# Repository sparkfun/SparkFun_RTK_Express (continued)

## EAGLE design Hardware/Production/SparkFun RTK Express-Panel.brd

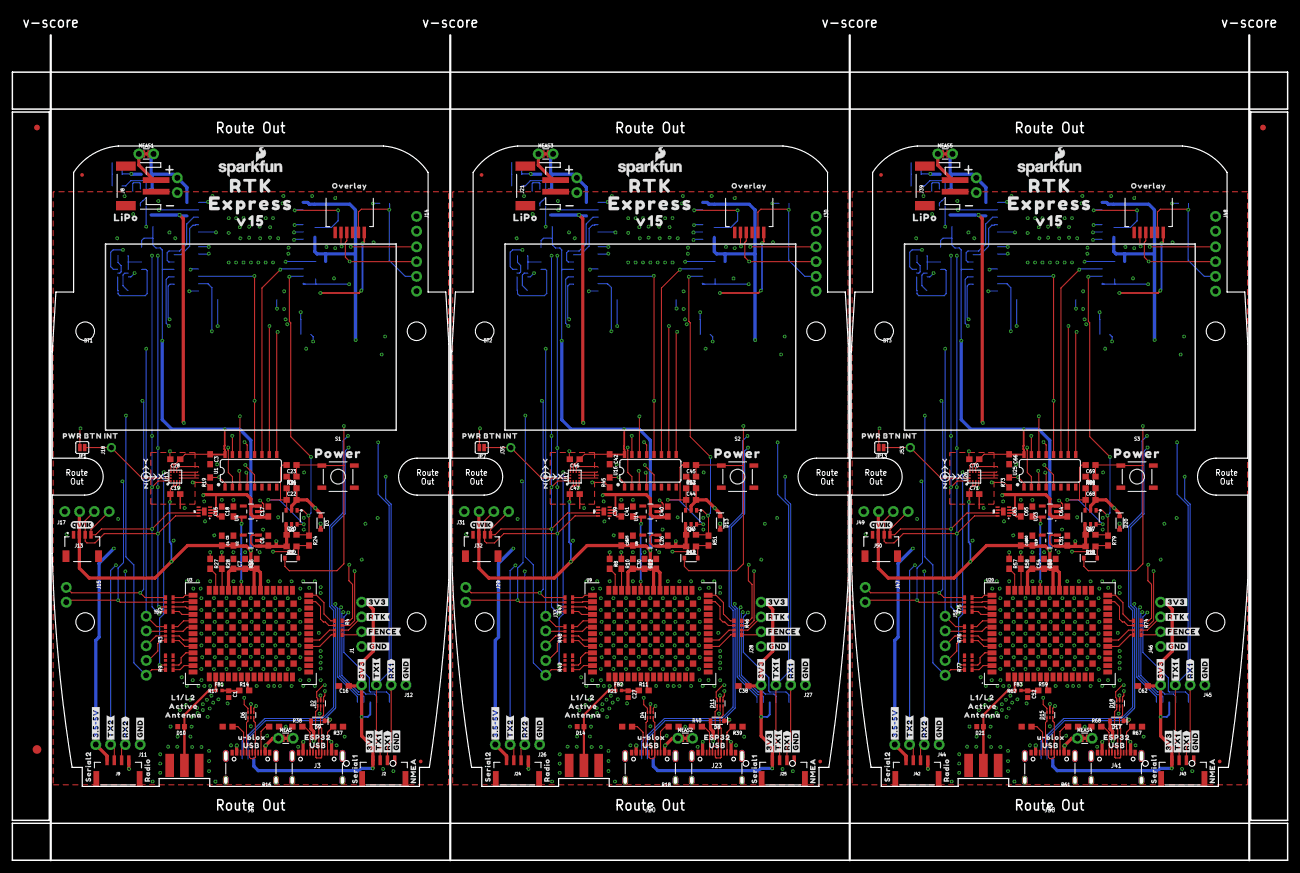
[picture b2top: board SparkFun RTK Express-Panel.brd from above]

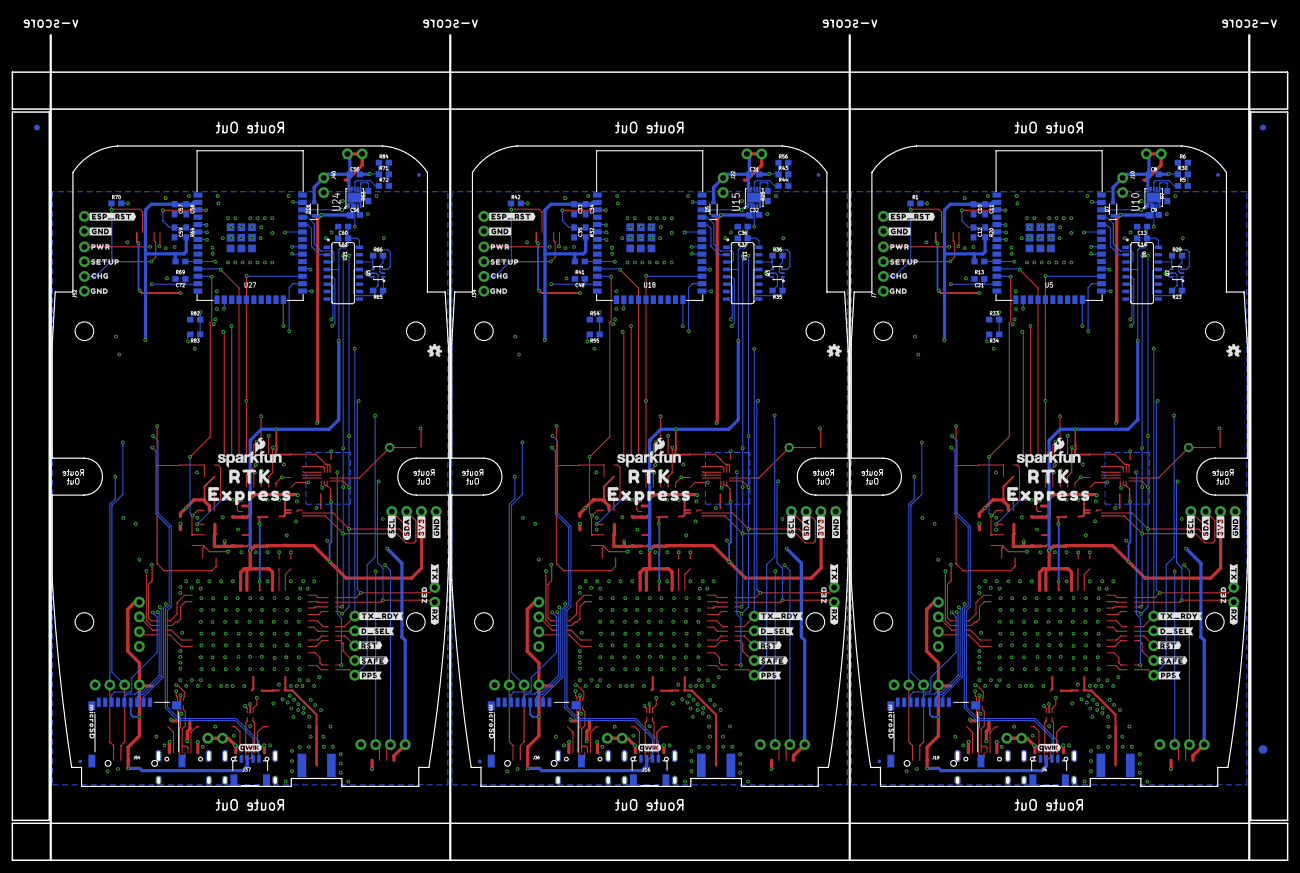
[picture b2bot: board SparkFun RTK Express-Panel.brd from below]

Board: 4 copper layers, 219.3 x 141.9 mm, 501 parts (165 on the bottom side), 258 nets.

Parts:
BT1, BT2, BT3: LIPO-OUTLINE1000; LIPO-1000
C1, C27, C52: 47pF; 0402
C2, C4, C6, C17, C18, C24, C26, C29, C40, C41, C49, C51, C53, C64, C65: 1.0uF; 0603
C3, C5, C7, C11, C12, C13, C15, C16, C21, C22, C23, C25, C28, C30, C34, C35, C36, C38, C39, C42, C44, C45, C46, C48, C50, C54, C58, C59, C60, C62, C63, C66, C68, C69, C70, C72: 0.1uF; 0603
C8, C9, C31, C32, C55, C56: 4.7uF; 0603
C10, C14, C19, C20, C33, C37, C43, C47, C57, C61, C67, C71: 10uF; 0603
D1, D12, D19: 250mA/100V; SOD-323
D2, D4, D6, D11, D15, D18: PRTR5V0U2F; SOT886
D3, D5, D7, D8, D9, D13, D16, D17, D20: 3A/10V/280mV; SOD-323
D10, D14, D21: PESD0402-0402; 0402
E1, E2, E3: SMA; SMA-EDGE
E$1, E$2, E$3, E$4: FIDUCIAL-1X2
E$5, E$6: FIDUCIAL-1.5X3
FB1, FB2, FB3: 2.66Ω; 0402-TIGHT
J1, J7, J11, J12, J26, J27, J28, J34, J44, J45, J46, J52: 1X04_NO_SILK
J2, J9, J24, J25, J42, J43: JST-4-SMD-1.25MM-LOCKING
J3, J5, J20, J23, J38, J41: USB Female Type C Connector; USB-C-16P_4LAYER-PADS
J4, J16, J37: External; JST04_1MM_RA
J6, J33, J51: 1X05_NO_SILK
J8, J21, J39: JST-2-SMD
J10, J14, J15, J22, J29, J30, J40, J47, J48: 1X02_NO_SILK
J13, J32, J50: Internal; JST04_1MM_RA
J17, J31, J49: Qwiic Right Angle; 1X04_NO_SILK
J18, J35, J53: 1X01_NO_SILK
J19, J36, J54: MICROSD; MICROSD-EXTERNALPIN
JP1, JP7, JP13: JUMPER-SMT_2_NO_SILK; SMT-JUMPER_2_NO_SILK
JP2, JP8, JP14: FPC_6_1MM-LIF
JP3, JP4, JP5, JP6, JP9, JP10, JP11, JP12, JP21, JP61, JP71, JP81: FIDUCIALUFIDUCIAL; FIDUCIAL-MICRO
LOGO1, LOGO4, LOGO7: OSHW-LOGOMINI; OSHW-LOGO-MINI
LOGO2, LOGO3, LOGO5, LOGO6, LOGO8, LOGO9: SFE_LOGO_NAME_FLAME.1_INCH; SFE_LOGO_NAME_FLAME_.1
MEAS, MEAS1, MEAS2, MEAS3, MEAS4, MEAS5: COMBO-JUMPER_2_NC_TRACE
Q1, Q4, Q6: SIL2308-TP; SOT26
Q2, Q3, Q5: MBT3904DW1T1; SC70-6
R1, R42, R70: 470; 0603
R2, R3, R4, R9, R46, R47, R48, R49, R74, R75, R76, R77: 33; 1206_RA
R5, R44, R72: 0; 0603
R6, R23, R29, R31, R34, R35, R36, R53, R55, R56, R65, R66, R81, R83, R84: 10k; 0603
R7, R19, R25, R45, R63, R73: 1k; 0603
R8, R10, R27, R28, R57, R58: 27; 0603
R11, R14, R59: 10; 0603
R12, R13, R15, R20, R22, R26, R32, R41, R50, R52, R60, R64, R69, R78, R80: 100k; 0603
R16, R17, R18, R21, R37, R38, R39, R40, R61, R62, R67, R68: 5.1k; 0603
R24, R51, R79: 300k; 0603
R30, R43, R71: 150k; 0603
R33, R54, R82: 3.3k; 0603
S1, S2, S3: Power; TACTILE_SWITCH_SMD_5.2MM
U1, U16, U25: 74HC4052D; SO16
U2, U8, U19: AP2112K-3.3; SOT23-5
U3, U9, U20: U-BLOX_ZED-F9P; ZED-F9P
U4, U14, U23: STLQ015-3.3V; SOT23-5
U5, U18, U27: ESP-WROOM-3232D; ESP-WROOM-32D
U6, U11, U21: CH340C; SO016
U7, U12, U22: MAX17048; DFN-8
U10, U15, U24: MCP73833; DFN-10
U13, U17, U26: LIS2DH12; LGA-12-LISDH12
U$1, U$19, U$38, U$48, U$63, U$64, U$82, U$95, U$127, U$140, U$141, U$157: #GND#0
U$2, U$30, U$93, U$106, U$125, U$168: QWIIC_4MM
U$3, U$107, U$169: #TX_RDY#0
U$4, U$118, U$180: INT0
U$5, U$12, U$37, U$47, U$62, U$91, U$126, U$139, U$154: #3V3#0
U$6, U$121, U$183: L1#L20
U$7, U$74, U$99, U$100, U$161, U$162: RTK0
U$8, U$120, U$182: OVERLAY0
U$9, U$119, U$181: PWR_BTN1
U$10, U$20, U$128: #RTK#1
U$11, U$78, U$148: #PPS#0
U$13, U$122, U$184: ACTIVE1
U$14, U$79, U$149: #RX#2
U$15, U$123, U$185: ANTENNA2
U$16, U$80, U$150: ZED0
U$17, U$75, U$145: ##SAFE##5
U$18, U$124, U$186: V150
U$21, U$26, U$129: 1553DBK-ENCLOSURE
U$22, U$27, U$130: LIPO0
U$23, U$77, U$147: #3#5#5V#0
U$24, U$115, U$177: X0
U$25, U$35, U$131: U#BLOX0
U$28, U$73, U$144: ##RST##4
U$29, U$54, U$134: SERIAL10
U$31, U$108, U$170: POWER0
U$32, U$76, U$146: #FENCE#3
U$33, U$109, U$171: CHG2
U$34, U$110, U$172: GND3
U$36, U$44, U$66, U$89, U$132, U$152: USB1
U$39, U$57, U$135: #RX2#2
U$40, U$58, U$136: #TX2#1
U$41, U$111, U$173: PWR0
U$42, U$112, U$174: SETUP1
U$43, U$52, U$133: SERIAL20
U$45, U$59, U$68, U$94, U$137, U$156: #RX1#2
U$46, U$61, U$65, U$92, U$138, U$155: #TX1#1
U$49, U$69, U$142: NMEA1
U$50, U$71, U$143: RADIO0
U$51, U$53, U$113, U$114, U$175, U$176: EXPRESS0
U$55, U$116, U$178: Y1
U$56, U$117, U$179: Z2
U$60, U$98, U$160: #ESP_RST#0
U$67, U$90, U$153: ESP320
U$70, U$101, U$163: #GND#2
U$72, U$81, U$151: #TX#1
U$83, U$96, U$158: MICROSD0
U$84, U$97, U$159: #GND#1
U$85, U$102, U$164: #3V3#2
U$86, U$103, U$165: #SCL#1
U$87, U$104, U$166: #SDA#0
U$88, U$105, U$167: #D_SEL#0

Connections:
3.3V: C2.1, C3.1, C4.1, C5.2, C7.2, C10.1, C11.1, C13.1, C14.1, C16.1, C19.1, C28.1, J1.4, J2.1, J4.2, J12.4, J13.2, J17.2, J19.4, R13.2, R15.2, R20.2, R34.2, U1.16, U2.5, U3.33, U3.34, U3.38, U5.2, U6.4, U6.16, U13.2, U13.3, U13.9, U13.10
3.3V1: C24.1, C25.2, C29.1, C30.2, C33.1, C34.1, C36.1, C37.1, C38.1, C42.1, C46.1, C47.1, J16.2, J25.1, J27.4, J28.4, J31.2, J32.2, J36.4, R12.2, R32.2, R41.2, R55.2, U8.5, U9.33, U9.34, U9.38, U11.4, U11.16, U16.16, U17.2, U17.3, U17.9, U17.10, U18.2
3.3V2: C49.1, C50.2, C53.1, C54.2, C57.1, C58.1, C60.1, C61.1, C62.1, C66.1, C70.1, C71.1, J37.2, J43.1, J45.4, J46.4, J49.2, J50.2, J54.4, R60.2, R64.2, R69.2, R83.2, U19.5, U20.33, U20.34, U20.38, U21.4, U21.16, U25.16, U26.2, U26.3, U26.9, U26.10, U27.2
ANT_VCC: C1.1, FB1.2, R14.1
ANT_VCC1: C27.1, FB2.2, R11.1
ANT_VCC2: C52.1, FB3.2, R59.1
CC1: J5.A5, R17.2
CC2: J5.B5, R16.2
CC3: J3.B5, R37.2
CC4: J3.A5, R38.2
CC5: J20.A5, R21.2
CC6: J20.B5, R18.2
CC7: J23.B5, R39.2
CC8: J23.A5, R40.2
CC9: J38.A5, R62.2
CC10: J38.B5, R61.2
CC11: J41.B5, R67.2
CC12: J41.A5, R68.2
CHG_LED: R1.2, U10.3
CHG_LED1: R42.2, U15.3
CHG_LED2: R70.2, U24.3
CHG_LED_RES: J7.2, JP2.2, R1.1
CHG_LED_RES1: J34.2, JP8.2, R42.1
CHG_LED_RES2: J52.2, JP14.2, R70.1
CHG_THERM1: R5.2, R6.2, R30.2
CHG_THERM2: R43.2, R44.2, R56.2
CHG_THERM3: R71.2, R72.2, R84.2
D+: D6.4, R27.1
D+1: D2.4, U6.5
D+2: D4.4, R8.1
D+3: D11.4, U11.5
D+4: D15.4, R57.1
D+5: D18.4, U21.5
D-: D6.6, R28.1
D-1: D2.6, U6.6
D-2: D4.6, R10.1
D-3: D11.6, U11.6
D-4: D15.6, R58.1
D-5: D18.6, U21.6
ESP32_!DTR: Q2.1, R23.1, U6.13
ESP32_!DTR1: Q3.1, R35.1, U11.13
ESP32_!DTR2: Q5.1, R65.1, U21.13
ESP32_!RTS: Q2.4, R29.1, U6.14
ESP32_!RTS1: Q3.4, R36.1, U11.14
ESP32_!RTS2: Q5.4, R66.1, U21.14
ESP32_EN: C12.1, J14.1, Q2.3, R20.1, U5.3
ESP32_EN1: C35.1, J30.1, Q3.3, R32.1, U18.3
ESP32_EN2: C59.1, J48.1, Q5.3, R64.1, U27.3
ESP32_RXI: U5.34, U6.2
ESP32_RXI1: U11.2, U18.34
ESP32_RXI2: U21.2, U27.34
ESP32_TXO: U5.35, U6.3
ESP32_TXO1: U11.3, U18.35
ESP32_TXO2: U21.3, U27.35
ESP_0/BOOT: Q2.6, U5.25
ESP_0/BOOT1: Q3.6, U18.25
ESP_0/BOOT2: Q5.6, U27.25
ESP_2/MUX_A: U1.10, U5.24
ESP_2/MUX_A1: U16.10, U18.24
ESP_2/MUX_A2: U25.10, U27.24
ESP_4/ACCEL_INT: J18.1, JP1.1, U13.12
ESP_4/ACCEL_INT1: J35.1, JP7.1, U17.12
ESP_4/ACCEL_INT2: J53.1, JP13.1, U26.12
ESP_4/MUX_B: U1.9, U5.26
ESP_4/MUX_B1: U16.9, U18.26
ESP_4/MUX_B2: U25.9, U27.26
ESP_13/POWER_CTRL: D1.A, R22.1, R24.2, U5.16
ESP_13/POWER_CTRL1: D12.A, R50.1, R51.2, U18.16
ESP_13/POWER_CTRL2: D19.A, R78.1, R79.2, U27.16
ESP_14/SETUP_BUTTON: C21.1, J7.3, JP2.4, U5.13
ESP_14/SETUP_BUTTON1: C48.1, J34.3, JP8.4, U18.13
ESP_14/SETUP_BUTTON2: C72.1, J52.3, JP14.4, U27.13
ESP_18/SCK: J19.5, U5.30
ESP_18/SCK1: J36.5, U18.30
ESP_18/SCK2: J54.5, U27.30
ESP_19/CIPO: J19.7, U5.31
ESP_19/CIPO1: J36.7, U18.31
ESP_19/CIPO2: J54.7, U27.31
ESP_21/SDA: J4.3, J13.3, J17.3, R2.P7, U1.2, U5.33, U7.8, U13.4
ESP_21/SDA1: J16.3, J31.3, J32.3, R47.P7, U12.8, U16.2, U17.4, U18.33
ESP_21/SDA2: J37.3, J49.3, J50.3, R75.P7, U22.8, U25.2, U26.4, U27.33
ESP_22/SCL: J4.4, J13.4, J17.4, R2.P8, U1.15, U5.36, U7.7, U13.1
ESP_22/SCL1: J16.4, J31.4, J32.4, R47.P8, U12.7, U16.15, U17.1, U18.36
ESP_22/SCL2: J37.4, J49.4, J50.4, R75.P8, U22.7, U25.15, U26.1, U27.36
ESP_23/COPI: J19.3, U5.37
ESP_23/COPI1: J36.3, U18.37
ESP_23/COPI2: J54.3, U27.37
ESP_25/SD_!CS!: J19.2, R13.1, U5.10
ESP_25/SD_!CS!1: J36.2, R41.1, U18.10
ESP_25/SD_!CS!2: J54.2, R69.1, U27.10
ESP_26/DAC1: U16.11, U18.11
ESP_26/DAC2: U1.11, U5.11
ESP_26/DAC3: U25.11, U27.11
ESP_26/ZED_TX_READY_LV: R3.P4, U3.46
ESP_26/ZED_TX_READY_LV1: R48.P4, U9.46
ESP_26/ZED_TX_READY_LV2: R76.P4, U20.46
ESP_27/FAST_OFF: C20.2, Q1.G1, R24.1, U5.12
ESP_27/FAST_OFF1: C43.2, Q4.G1, R51.1, U18.12
ESP_27/FAST_OFF2: C67.2, Q6.G1, R79.1, U27.12
ESP_D1+: D2.3, J3.A6, J3.B6
ESP_D1+1: D11.3, J23.A6, J23.B6
ESP_D1+2: D18.3, J41.A6, J41.B6
ESP_D1-: D2.1, J3.A7, J3.B7
ESP_D1-1: D11.1, J23.A7, J23.B7
ESP_D1-2: D18.1, J41.A7, J41.B7
ESP_I16/ZED-TXO1: J15.1, R2.P5, U1.12, U5.27
ESP_I16/ZED-TXO2: J29.1, R47.P5, U16.12, U18.27
ESP_I16/ZED-TXO3: J47.1, R75.P5, U25.12, U27.27
ESP_I34/ZED_TX_READY: J6.1, R3.P5, U5.6
ESP_I34/ZED_TX_READY1: J33.1, R48.P5, U18.6
ESP_I34/ZED_TX_READY2: J51.1, R76.P5, U27.6
ESP_I35/DEVICE_SENSE: R33.2, R34.1, U5.7
ESP_I35/DEVICE_SENSE1: R54.2, R55.1, U18.7
ESP_I35/DEVICE_SENSE2: R82.2, R83.1, U27.7
ESP_I39/ADC1: U16.4, U18.5
ESP_I39/ADC2: U25.4, U27.5
ESP_I39/ADC39: U1.4, U5.5
ESP_O17/ZED-RXI1: J15.2, R2.P6, R19.2, U1.1
ESP_O17/ZED-RXI2: J29.2, R45.2, R47.P6, U16.1
ESP_O17/ZED-RXI3: J47.2, R73.2, R75.P6, U25.1
EXTERNAL_DATA_IN: J2.3, J12.2, U1.3
EXTERNAL_DATA_IN1: J25.3, J27.2, U16.3
EXTERNAL_DATA_IN2: J43.3, J45.2, U25.3
EXTERNAL_DATA_OUT: J2.2, J12.3, U1.13
EXTERNAL_DATA_OUT1: J25.2, J27.3, U16.13
EXTERNAL_DATA_OUT2: J43.2, J45.3, U25.13
EXTINT_LV: R9.P2, U3.51
EXTINT_LV1: R49.P2, U9.51
EXTINT_LV2: R77.P2, U20.51
FENCE_LV: R4.P4, U3.19
FENCE_LV1: R46.P4, U9.19
FENCE_LV2: R74.P4, U20.19
GND: C1.2, C2.2, C3.2, C4.2, C5.1, C6.2, C7.1, C8.2, C9.2, C10.2, C11.2, C12.2, C13.2, C14.2, C15.2, C16.2, C17.2, C18.2, C19.2, C21.2, C28.2, D2.2, D6.2, D10.2, E1.GND@0, E1.GND@1, E1.GND@2, E1.GND@3, J1.1, J2.4, J3.GND, J3.GND2, J3.SHLD1, J3.SHLD2, J3.SHLD3, J3.SHLD4, J4.1, J5.GND, J5.GND2, J5.SHLD1, J5.SHLD2, J5.SHLD3, J5.SHLD4, J7.1, J8.1, J9.4, J10.2, J11.1, J12.1, J13.1, J14.2, J17.1, J19.6, J19.9, J19.10, J19.11, J19.12, J19.13, JP2.6, Q1.S1, R6.1, R7.1, R15.1, R16.1, R17.1, R30.1, R33.1, R37.1, R38.1, S1.3, U1.6, U1.7, U1.8, U2.2, U3.1, U3.3, U3.12, U3.14, U3.32, U3.37, U3.41, U3.48, U3.55, U3.56, U3.57, U3.58, U3.59, U3.60, U3.61, U3.62, U3.63, U3.64, U3.65, U3.66, U3.67, U3.68, U3.69, U3.70, U3.71, U3.72, U3.73, U3.74, U3.75, U3.76, U3.77, U3.78, U3.79, U3.80, U3.81, U3.82, U3.83, U3.84, U3.85, U3.86, U3.87, U3.88, U3.89, U3.90, U3.91, U3.92, U3.93, U3.94, U3.95, U3.96, U3.97, U3.98, U3.99, U3.100, U3.101, U3.102, U4.2, U5.1, U5.15, U5.38, U5.GND, U5.GNDT1, U5.GNDT2, U5.GNDT3, U5.GNDT4, U5.GNDT5, U5.GNDT6, U5.GNDT7, U5.GNDT8, U6.1, U7.1, U7.4, U7.6, U7.9, U10.5, U10.11, U13.5, U13.6, U13.7, U13.8
GND1: C24.2, C25.1, C26.2, C27.2, C29.2, C30.1, C31.2, C32.2, C33.2, C34.2, C35.2, C36.2, C37.2, C38.2, C39.2, C40.2, C41.2, C42.2, C46.2, C47.2, C48.2, D4.2, D11.2, D14.2, E2.GND@0, E2.GND@1, E2.GND@2, E2.GND@3, J16.1, J20.GND, J20.GND2, J20.SHLD1, J20.SHLD2, J20.SHLD3, J20.SHLD4, J21.1, J22.2, J23.GND, J23.GND2, J23.SHLD1, J23.SHLD2, J23.SHLD3, J23.SHLD4, J24.4, J25.4, J26.1, J27.1, J28.1, J30.2, J31.1, J32.1, J34.1, J36.6, J36.9, J36.10, J36.11, J36.12, J36.13, JP8.6, Q4.S1, R12.1, R18.1, R21.1, R25.1, R39.1, R40.1, R43.1, R54.1, R56.1, S2.3, U8.2, U9.1, U9.3, U9.12, U9.14, U9.32, U9.37, U9.41, U9.48, U9.55, U9.56, U9.57, U9.58, U9.59, U9.60, U9.61, U9.62, U9.63, U9.64, U9.65, U9.66, U9.67, U9.68, U9.69, U9.70, U9.71, U9.72, U9.73, U9.74, U9.75, U9.76, U9.77, U9.78, U9.79, U9.80, U9.81, U9.82, U9.83, U9.84, U9.85, U9.86, U9.87, U9.88, U9.89, U9.90, U9.91, U9.92, U9.93, U9.94, U9.95, U9.96, U9.97, U9.98, U9.99, U9.100, U9.101, U9.102, U11.1, U12.1, U12.4, U12.6, U12.9, U14.2, U15.5, U15.11, U16.6, U16.7, U16.8, U17.5, U17.6, U17.7, U17.8, U18.1, U18.15, U18.38, U18.GND, U18.GNDT1, U18.GNDT2, U18.GNDT3, U18.GNDT4, U18.GNDT5, U18.GNDT6, U18.GNDT7, U18.GNDT8
GND2: C49.2, C50.1, C51.2, C52.2, C53.2, C54.1, C55.2, C56.2, C57.2, C58.2, C59.2, C60.2, C61.2, C62.2, C63.2, C64.2, C65.2, C66.2, C70.2, C71.2, C72.2, D15.2, D18.2, D21.2, E3.GND@0, E3.GND@1, E3.GND@2, E3.GND@3, J37.1, J38.GND, J38.GND2, J38.SHLD1, J38.SHLD2, J38.SHLD3, J38.SHLD4, J39.1, J40.2, J41.GND, J41.GND2, J41.SHLD1, J41.SHLD2, J41.SHLD3, J41.SHLD4, J42.4, J43.4, J44.1, J45.1, J46.1, J48.2, J49.1, J50.1, J52.1, J54.6, J54.9, J54.10, J54.11, J54.12, J54.13, JP14.6, Q6.S1, R60.1, R61.1, R62.1, R63.1, R67.1, R68.1, R71.1, R82.1, R84.1, S3.3, U19.2, U20.1, U20.3, U20.12, U20.14, U20.32, U20.37, U20.41, U20.48, U20.55, U20.56, U20.57, U20.58, U20.59, U20.60, U20.61, U20.62, U20.63, U20.64, U20.65, U20.66, U20.67, U20.68, U20.69, U20.70, U20.71, U20.72, U20.73, U20.74, U20.75, U20.76, U20.77, U20.78, U20.79, U20.80, U20.81, U20.82, U20.83, U20.84, U20.85, U20.86, U20.87, U20.88, U20.89, U20.90, U20.91, U20.92, U20.93, U20.94, U20.95, U20.96, U20.97, U20.98, U20.99, U20.100, U20.101, U20.102, U21.1, U22.1, U22.4, U22.6, U22.9, U23.2, U24.5, U24.11, U25.6, U25.7, U25.8, U26.5, U26.6, U26.7, U26.8, U27.1, U27.15, U27.38, U27.GND, U27.GNDT1, U27.GNDT2, U27.GNDT3, U27.GNDT4, U27.GNDT5, U27.GNDT6, U27.GNDT7, U27.GNDT8
GPS_ANT1: D10.1, E1.SIG, FB1.1, U3.2
GPS_ANT2: D14.1, E2.SIG, FB2.1, U9.2
GPS_ANT3: D21.1, E3.SIG, FB3.1, U20.2
LIPO_RAW: J8.2, MEAS1.1, MEAS1.3
LIPO_RAW1: J21.2, MEAS3.1, MEAS3.3
LIPO_RAW2: J39.2, MEAS5.1, MEAS5.3
unnamed: R8.2, U9.40
unnamed: R10.2, U9.39
unnamed: R11.2, U9.7
unnamed: J5.VBUS1, J5.VBUS2, MEAS.1, MEAS.3
unnamed: R5.1, U10.8
unnamed: R19.1, U5.28
unnamed: Q3.5, R35.2
unnamed: Q3.2, R36.2
unnamed: D8.A, J23.VBUS1, J23.VBUS2
unnamed: J20.VBUS1, J20.VBUS2, MEAS2.1, MEAS2.3
unnamed: R27.2, U3.40
unnamed: R28.2, U3.39
unnamed: R14.2, U3.7
unnamed: R44.1, U15.8
unnamed: C22.1, C23.2, Q1.D1, Q1.G2, R26.1
unnamed: R45.1, U18.28
unnamed: C44.1, C45.2, Q4.D1, Q4.G2, R52.1
unnamed: R57.2, U20.40
unnamed: R58.2, U20.39
unnamed: R59.2, U20.7
unnamed: Q5.5, R65.2
unnamed: Q5.2, R66.2
unnamed: D17.A, J41.VBUS1, J41.VBUS2
unnamed: Q2.5, R23.2
unnamed: Q2.2, R29.2
unnamed: J38.VBUS1, J38.VBUS2, MEAS4.1, MEAS4.3
unnamed: R72.1, U24.8
unnamed: R73.1, U27.28
unnamed: C68.1, C69.2, Q6.D1, Q6.G2, R80.1
unnamed: D9.A, J3.VBUS1, J3.VBUS2
POWER_BTN: C23.1, D1.C, J7.4, JP1.2, JP2.5, R31.1, S1.1
POWER_BTN1: C45.1, D12.C, J34.4, JP7.2, JP8.5, R53.1, S2.1
POWER_BTN2: C69.1, D19.C, J52.4, JP13.2, JP14.5, R81.1, S3.1
PPS: R9.P1, U3.53
PPS1: R49.P1, U9.53
PPS2: R77.P1, U20.53
PROG1: R7.2, U10.6
PROG2: R25.2, U15.6
PROG3: R63.2, U24.6
RTK_LV: R4.P3, U3.20
RTK_LV1: R46.P3, U9.20
RTK_LV2: R74.P3, U20.20
RX2_LV: R4.P2, U3.26
RX2_LV1: R46.P2, U9.26
RX2_LV2: R74.P2, U20.26
RXLV: R2.P3, U3.43
RXLV1: R47.P3, U9.43
RXLV2: R75.P3, U20.43
SCL_LV: R2.P1, U3.45
SCL_LV1: R47.P1, U9.45
SCL_LV2: R75.P1, U20.45
SDA_LV: R2.P2, U3.44
SDA_LV1: R47.P2, U9.44
SDA_LV2: R75.P2, U20.44
TX2_LV: R4.P1, U3.27
TX2_LV1: R46.P1, U9.27
TX2_LV2: R74.P1, U20.27
TXLV: R2.P4, U3.42
TXLV1: R47.P4, U9.42
TXLV2: R75.P4, U20.42
UNP_D+: D6.3, J5.A6, J5.B6
UNP_D+1: D4.3, J20.A6, J20.B6
UNP_D+2: D15.3, J38.A6, J38.B6
UNP_D-: D6.1, J5.A7, J5.B7
UNP_D-1: D4.1, J20.A7, J20.B7
UNP_D-2: D15.1, J38.A7, J38.B7
VOUT: C6.1, C20.1, J9.1, J11.4, Q1.D2, R22.2, U2.1, U2.3
VOUT1: C26.1, C43.1, J24.1, J26.4, Q4.D2, R50.2, U8.1, U8.3
VOUT2: C51.1, C67.1, J42.1, J44.4, Q6.D2, R78.2, U19.1, U19.3
V_BATT: C8.1, C15.1, C17.1, D7.A, J10.1, MEAS1.2, MEAS1.4, U4.1, U4.3, U7.2, U7.3, U10.9, U10.10
V_BATT1: C31.1, C39.1, C40.1, D5.A, J22.1, MEAS3.2, MEAS3.4, U12.2, U12.3, U14.1, U14.3, U15.9, U15.10
V_BATT2: C55.1, C63.1, C64.1, D16.A, J40.1, MEAS5.2, MEAS5.4, U22.2, U22.3, U23.1, U23.3, U24.9, U24.10
V_BKCP: C18.1, U3.36, U4.5
V_BKCP1: C41.1, U9.36, U14.5
V_BKCP2: C65.1, U20.36, U23.5
V_RAW: C9.1, C22.2, D3.C, D7.C, Q1.S2, R26.2, R31.2, U10.1, U10.2
V_RAW1: C32.1, C44.2, D5.C, D13.C, Q4.S2, R52.2, R53.2, U15.1, U15.2
V_RAW2: C56.1, C68.2, D16.C, D20.C, Q6.S2, R80.2, R81.2, U24.1, U24.2
V_USB: D2.5, D3.A, D6.5, D9.C, JP2.1, MEAS.2, MEAS.4
V_USB1: D4.5, D8.C, D11.5, D13.A, JP8.1, MEAS2.2, MEAS2.4
V_USB2: D15.5, D17.C, D18.5, D20.A, JP14.1, MEAS4.2, MEAS4.4
ZED-RXI1: J24.3, J26.2, R46.P7
ZED-RXI2: J9.3, J11.2, R4.P7
ZED-RXI3: J42.3, J44.2, R74.P7
ZED-TXO1: J24.2, J26.3, R46.P8
ZED-TXO2: J9.2, J11.3, R4.P8
ZED-TXO3: J42.2, J44.3, R74.P8
ZED_!RESET!: J6.3, R3.P7
ZED_!RESET!1: J33.3, R48.P7
ZED_!RESET!2: J51.3, R76.P7
ZED_!RESET!_LV: R3.P2, U3.49
ZED_!RESET!_LV1: R48.P2, U9.49
ZED_!RESET!_LV2: R76.P2, U20.49
ZED_!SAFE!: J6.4, R3.P8
ZED_!SAFE!1: J33.4, R48.P8
ZED_!SAFE!2: J51.4, R76.P8
ZED_!SAFE!_LV: R3.P1, U3.50
ZED_!SAFE!_LV1: R48.P1, U9.50
ZED_!SAFE!_LV2: R76.P1, U20.50
ZED_D_SEL: J6.2, R3.P6
ZED_D_SEL1: J33.2, R48.P6
ZED_D_SEL2: J51.2, R76.P6
ZED_D_SEL_LV: R3.P3, U3.47
ZED_D_SEL_LV1: R48.P3, U9.47
ZED_D_SEL_LV2: R76.P3, U20.47
ZED_EXTINT: R9.P7, U1.5
ZED_EXTINT1: R49.P7, U16.5
ZED_EXTINT2: R77.P7, U25.5
ZED_FENCE_STAT: J1.2, R4.P5
ZED_FENCE_STAT1: J28.2, R46.P5
ZED_FENCE_STAT2: J46.2, R74.P5
ZED_PPS_STAT: J6.5, R9.P8, U1.14
ZED_PPS_STAT1: J33.5, R49.P8, U16.14
ZED_PPS_STAT2: J51.5, R77.P8, U25.14
ZED_RTK_STAT: J1.3, R4.P6
ZED_RTK_STAT1: J28.3, R46.P6
ZED_RTK_STAT2: J46.3, R74.P6

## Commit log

2021-02-24 Add firmware
2021-02-24 New state machine. Faster display updates. More graphics.
2021-02-24 Change Surveyor to Express in firmware
2021-02-24 Add display during serial config. Add min HPA before survey-in start.
2021-02-24 Control base/rover state based on power button tap
2021-03-04 Ready v11. Redo GND layers for panelizer.
2021-03-04 Add tilt test sketches
2021-03-04 Add helper displays for base/rover switching.
2021-03-04 Remove old libraries
2021-03-05 Add menu and NVM support for mux control.
2021-03-19 Update FP and PROD ID on ESP32 module
2021-03-26 Update graphics
2021-04-13 Modify toolpath for 1/16" Bit
2021-04-16 Move radio to power control. Add ESD to GNSS RF. Move overlay connector.
2021-04-16 Remove old sketch
2021-04-16 Add BT pin support. Add accel support. Increase xTask sizes. Increase I2C to 400kHz.
2021-04-16 Add online check for fuel gauge.
2021-04-16 Move test menu to display.
2021-04-16 Add test sketches for display, and accel.
2021-04-16 Add test sketches for Sound Trigger logging.
2021-04-16 Remove old overlay files
2021-04-16 Update v12 panel files.
2021-04-16 Update panel file to v12
2021-04-16 Add PROD_ID for PESD diode.
2021-06-01 Remove old firmware
    Combined with RTK Surveyor.
2021-06-01 Add test sketches
2021-06-01 Add SVG logo
2021-06-01 Shuffle schematic elements to fit into frame.
2021-06-09 Removing redundant firmware files.
    For RTK Firmware see: https://github.com/sparkfun/SparkFun_RTK_Firmware
2021-06-17 Move to non-SMD SMA. Change to push-push microSD.
2021-06-17 Move microSD socket further out.
2021-07-01 Remove push pull SD socket. v13 PCB
2021-07-01 v13 PCB. Add panel. Change from SMD SMA To edge mount SMD to increase strength of connector.
2021-07-01 Remove old single board test files
2021-09-29 Update links to product. Add Logo png.
2022-02-03 Remove graphics (moved to Firmware repo)
2022-02-03 Update issue templates
2022-02-24 v14 - Remove ground plane from around accelerometer
2022-03-07 Remove groundplane from around accel. Switch to wider ESP FP, exposed pin microSD, CH340 with VCC from USB.
    Increase paste on 12-pin FPC connector.
2022-03-07 Remove old files
2022-03-07 New production files for v14 PCB.
2022-03-07 Add impendence control note
2022-03-30 Add route out note
2022-04-11 LIF overlay connector, accel plane removal, full ESP32 FP.
2022-05-18 v15. Fix tCream on LIF connector. Correct CH340 3.3V.
2022-05-18 Production files for v15
2022-05-19 Add ID panel
2024-12-20 Add enclosure 3D file

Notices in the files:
parts and their libraries:
SparkFun-Resistors: Licensing: Creative Commons ShareAlike 4.0 International - https://creativecommons.org/licenses/by-sa/4.0
